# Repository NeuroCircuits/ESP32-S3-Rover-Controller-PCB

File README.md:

# ESP32-S3-Rover-Controller-PCB
Custom ESP32-S3 based controller PCB for a 6-wheel robotic platform, featuring servo control, DC motor drivers, IMU, RFID, USB programming, and dedicated power regulation.

## Overview

This project is a custom controller PCB designed for a mobile robotic platform.

The board is built around the ESP32-S3-WROOM-1U and integrates the main electronics required for controlling the robot, reducing the need for separate wiring and controller boards.

The PCB was designed from schematic to final PCB layout in KiCad, including routing, power distribution, grounding, mounting holes, design-rule checking, and Gerber generation.

## Features

- ESP32-S3-WROOM-1U main controller
- USB Type-C programming interface
- USB-to-UART interface
- Automatic programming / reset circuitry
- PCA9685 16-channel PWM controller
- Support for multiple high-torque servos
- Interfaces for 4 × BTS motor-driver modules
- Control for 6 DC motors
- MPU6050 IMU interface
- RC522 RFID interface
- 3.3 V regulated supply for logic
- 5 V regulated supply
- Dedicated 6 V servo power rail
- High-current power input
- Main power switching
- Fuse protection
- Multiple bulk and decoupling capacitors
- Through-hole mounting holes
- Two-layer PCB
- Custom copper power and GND planes

- ## PCB Design

Designed using KiCad.

The design includes:

- Schematic capture
- Component selection and footprint assignment
- PCB layout
- Power and ground distribution
- Signal routing
- Copper zones
- Mounting holes
- Silkscreen labeling
- Design Rule Check (DRC)
- Gerber generation

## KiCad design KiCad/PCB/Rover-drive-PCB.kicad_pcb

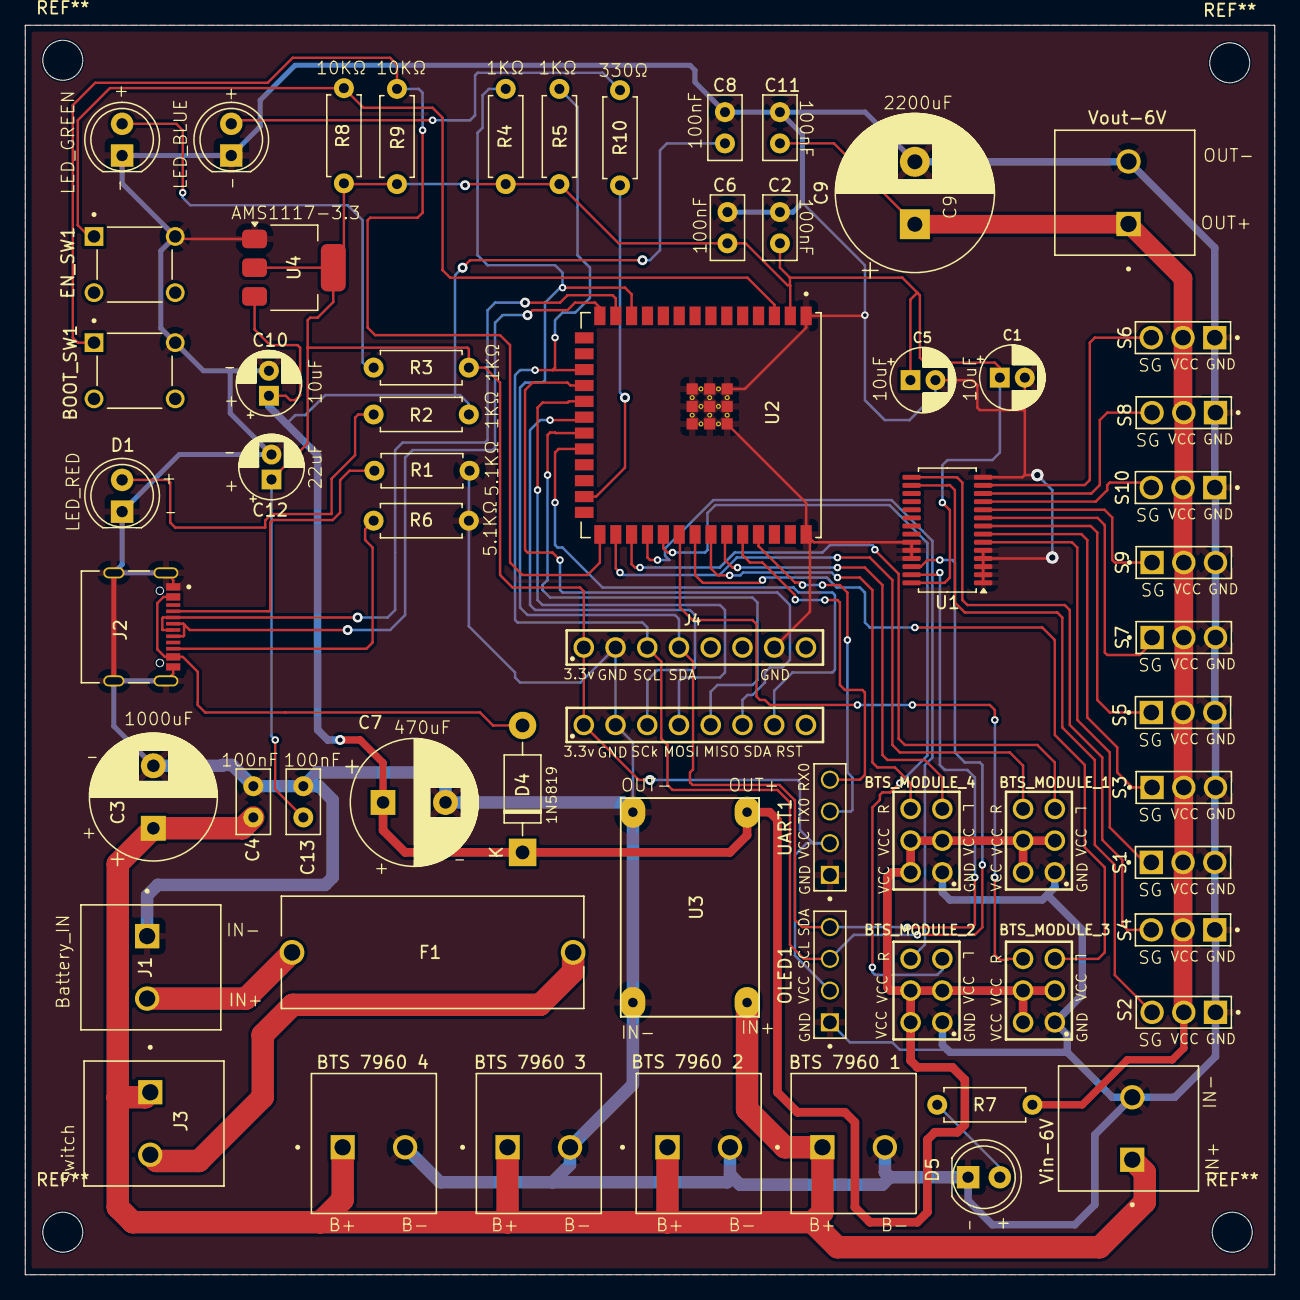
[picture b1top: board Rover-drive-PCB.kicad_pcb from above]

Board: 2 copper layers, 100.0 x 100.0 mm, 62 parts (0 on the bottom side), 46 nets.

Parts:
BOOT_SW1: S2; 4_pin_tacticle_push_button
BTS 7960 1, BTS 7960 2, BTS 7960 3, BTS 7960 4: 1711026; PHOENIX_1711026
BTS_MODULE_1, BTS_MODULE_2, BTS_MODULE_3, BTS_MODULE_4: 6130XX21121_61300621121; 61300621121
C1: 10uF (Servo driver); CP_Radial_D5.0mm_P2.00mm
C2: 100nF (servo driver); C_Disc_D5.0mm_W2.5mm_P2.50mm
C3: 1000uF (for main power rail); CP_Radial_D10.0mm_P5.00mm
C4: 100nF ( for power rail); C_Disc_D5.0mm_W2.5mm_P2.50mm
C5: 10uF (with esp32); CP_Radial_D5.0mm_P2.00mm
C6: 100nF (esp); C_Disc_D5.0mm_W2.5mm_P2.50mm
C7: 470uF (5v buck); CP_Radial_D10.0mm_P5.00mm
C8: 100nF (5v buck); C_Disc_D5.0mm_W2.5mm_P2.50mm
C9: 2200uF (6v buck); CP_Radial_D12.5mm_P5.00mm
C10: 10uF (5v regulator); CP_Radial_D5.0mm_P2.00mm
C11: 100nF (6v buck); C_Disc_D5.0mm_W2.5mm_P2.50mm
C12: 22uF (3.3v regulator); CP_Radial_D5.0mm_P2.00mm
C13: 100nF (3.3v buck); C_Disc_D5.0mm_W2.5mm_P2.50mm
D1: power_led; LED_D5.0mm
D2: buck 3.3v led; LED_D5.0mm
D4: 1N5819; D_DO-41_SOD81_P10.16mm_Horizontal
D5: servo_led; LED_D5.0mm
D6: status_led; LED_D5.0mm
EN_SW1: S1; 4_pin_tacticle_push_button
F1: Fuse; FUSE_4628
J1: 2 pin screw terminal; PHOENIX_1711026
J2: TYPE-C-31-M-12; HRO_TYPE-C-31-M-12
J3: 2 pin screw terminal for button; PHOENIX_1711026
J4: MPU6050; 61300811121
J5: RC522; 61300811121
OLED1: 61300411121; WURTH_61300411121
R1, R6: 5.1k; R_Axial_DIN0207_L6.3mm_D2.5mm_P7.62mm_Horizontal
R2, R3, R4, R5, R7: 1k; R_Axial_DIN0207_L6.3mm_D2.5mm_P7.62mm_Horizontal
R8, R9: 10k; R_Axial_DIN0207_L6.3mm_D2.5mm_P7.62mm_Horizontal
R10: 330; R_Axial_DIN0207_L6.3mm_D2.5mm_P7.62mm_Horizontal
S1, S2, S3, S4, S5, S6, S7, S8, S9, S10: 61300311121; 3_pin_male_header
U1: PCA9685PW; TSSOP-28_4.4x9.7mm_P0.65mm
U2: ESP32-S3-WROOM-1U-N8R8; XCVR_ESP32-S3-WROOM-1U-N8R8
U3: buck converter 5v; Mini360_step-down (3)
U4: AMS1117-3.3; SOT-223-3_TabPin2
UART1: 61300411121; WURTH_61300411121
Vin-6V: 1711026; PHOENIX_1711026
Vout-6V: 1711026; PHOENIX_1711026

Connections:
/3.3v: C1.1, C2.1, C5.1, C6.1, C12.1, C13.1, J4.1, J5.1, OLED1.02, R3.1, R4.1, R5.1, R8.1, R9.2, U1.28 (VDD), U2.2 (3V3), U4.2 (VO), UART1.02
/5v: BTS_MODULE_1.2, BTS_MODULE_1.3, BTS_MODULE_1.4, BTS_MODULE_2.2, BTS_MODULE_2.3, BTS_MODULE_2.4, BTS_MODULE_3.2, BTS_MODULE_3.3, BTS_MODULE_3.4, BTS_MODULE_4.2, BTS_MODULE_4.3, BTS_MODULE_4.4, C7.1, C8.1, C10.1, D4.1 (K), R2.1, U3.4 (OUT+), U4.3 (VI)
/L_pwm_1: BTS_MODULE_4.5, U2.29 (IO36)
/L_pwm_2: BTS_MODULE_3.5, U2.31 (IO38)
/L_pwm_3: BTS_MODULE_2.5, U2.33 (IO40)
/L_pwm_4: BTS_MODULE_1.5, U2.35 (IO42)
/MISO: J5.5, U2.21 (IO13)
/MOSI: J5.4, U2.19 (IO11)
/RC522_RST: J5.7, U2.22 (IO14)
/RC522_SDA: J5.6, U2.18 (IO10)
/RX0: U2.36 (RXD0), UART1.04
/R_pwm_1: BTS_MODULE_4.6, U2.28 (IO35)
/R_pwm_2: BTS_MODULE_3.6, U2.30 (IO37)
/R_pwm_3: BTS_MODULE_2.6, U2.32 (IO39)
/R_pwm_4: BTS_MODULE_1.6, U2.34 (IO41)
/S0: S1.1, U1.6 (LED0)
/S1: S3.1, U1.7 (LED1)
/S2: S5.1, U1.8 (LED2)
/S3: S7.1, U1.9 (LED3)
/S4: S9.1, U1.10 (LED4)
/S5: S10.3, U1.11 (LED5)
/S6: S8.3, U1.12 (LED6)
/S7: S6.3, U1.13 (LED7)
/S8: S4.3, U1.15 (LED8)
/S9: S2.3, U1.16 (LED9)
/SCK: J5.3, U2.20 (IO12)
/SCL: J4.3, OLED1.03, R5.2, U1.26 (SCL), U2.17 (IO9)
/SDA: J4.4, OLED1.04, R4.2, U1.27 (SDA), U2.12 (IO8)
/Servo_VCC: C9.1, C11.1, R7.1, S1.2, S2.2, S3.2, S4.2, S5.2, S6.2, S7.2, S8.2, S9.2, S10.2, Vout-6V.1
/TX0: U2.37 (TXD0), UART1.03
/V_in: BTS 7960 1.1, BTS 7960 2.1, BTS 7960 3.1, BTS 7960 4.1, C3.1, C4.1, J3.1, U3.2 (IN+), Vin-6V.1
/usb d+: J2.A6 (DP1), J2.B6 (DP2), U2.14 (IO20)
/usb d-: J2.A7 (DN1), J2.B7 (DN2), U2.13 (IO19)
GND: BOOT_SW1.2 (B), BTS 7960 1.2, BTS 7960 2.2, BTS 7960 3.2, BTS 7960 4.2, BTS_MODULE_1.1, BTS_MODULE_2.1, BTS_MODULE_3.1, BTS_MODULE_4.1, C1.2, C2.2, C3.2, C4.2, C5.2, C6.2, C7.2, C8.2, C9.2, C10.2, C11.2, C12.2, C13.2, D1.1 (K), D2.1 (K), D5.1 (K), D6.1 (K), EN_SW1.2 (B), J1.1, J2.A1_B12 (GND), J2.B1_A12 (GND), J2.S1 (SHIELD), J2.S2 (SHIELD), J2.S3 (SHIELD), J2.S4 (SHIELD), J4.2, J4.7, J5.2, OLED1.01, R1.1, R6.2, S1.3, S2.1, S3.3, S4.1, S5.3, S6.1, S7.3, S8.1, S9.3, S10.1, U1.1 (A0), U1.2 (A1), U1.3 (A2), U1.4 (A3), U1.5 (A4), U1.14 (VSS), U1.23 (~OE), U1.24 (A5), U1.25 (EXTCLK), U2.1 (GND), U2.40 (GND), U2.41_1 (GND), U2.41_2 (GND), U2.41_3 (GND), U2.41_4 (GND), U2.41_5 (GND), U2.41_6 (GND), U2.41_7 (GND), U2.41_8 (GND), U2.41_9 (GND), U2.41_10, U2.41_11, U2.41_12, U2.41_13, U2.41_14, U2.41_15, U2.41_16, U2.41_17, U2.41_18, U2.41_19, U2.41_20, U2.41_21, U3.1 (IN-), U3.3 (OUT-), U4.1 (GND), UART1.01, Vin-6V.2, Vout-6V.2
unnamed: BOOT_SW1.1 (A), R9.1, U2.27 (IO0)
unnamed: D1.2 (A), R2.2
unnamed: D2.2 (A), R3.2
unnamed: D5.2 (A), R7.2
unnamed: D6.2 (A), R10.2
unnamed: EN_SW1.1 (A), R8.2, U2.3 (EN)
unnamed: F1.1, J1.2
unnamed: F1.2, J3.2
unnamed: J2.A5 (CC1), R1.2
unnamed: J2.B5 (CC2), R6.1
unnamed: R10.1, U2.25 (IO48)
VBUS: D4.2 (A), J2.A4_B9 (VBUS), J2.B4_A9 (VBUS)
